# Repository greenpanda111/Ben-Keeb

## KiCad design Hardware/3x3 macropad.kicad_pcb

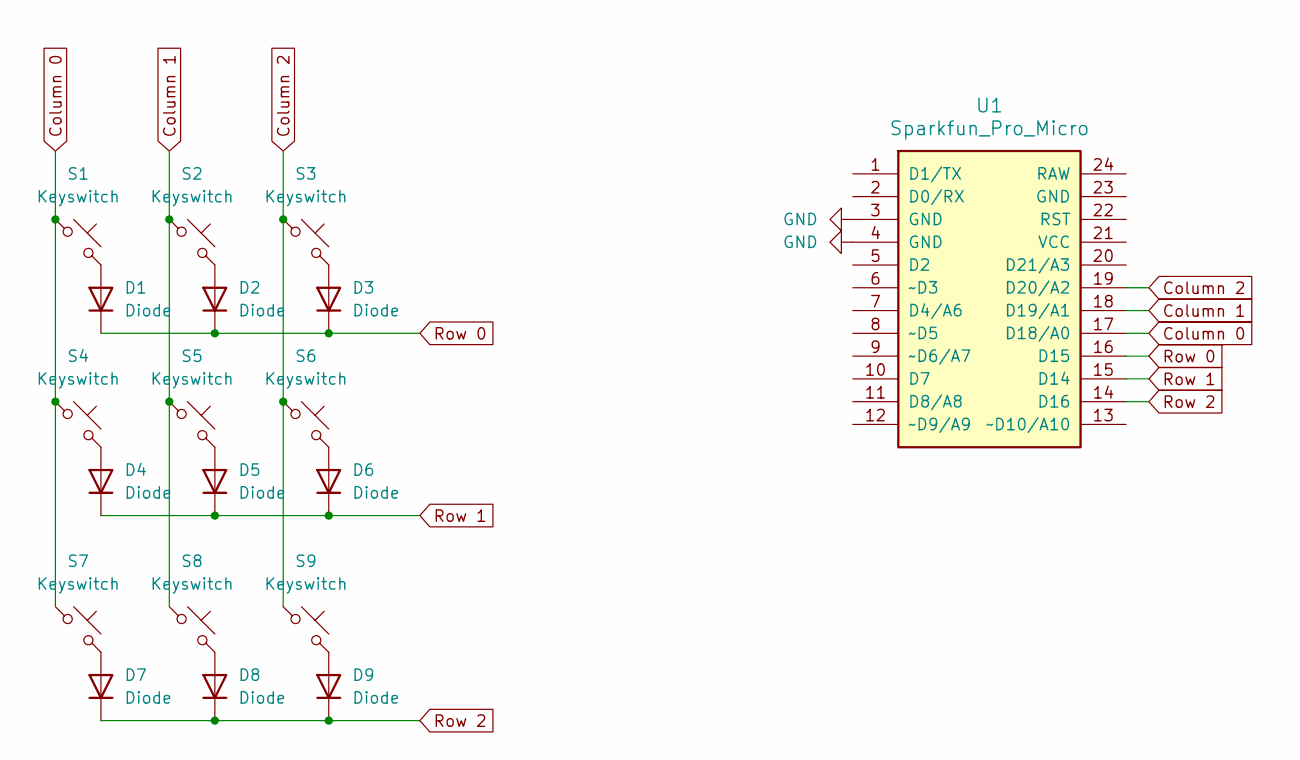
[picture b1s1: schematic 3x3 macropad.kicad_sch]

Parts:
D1, D2, D3, D4, D5, D6, D7, D8, D9: Diode; Diode_DO-35
S1, S2, S3, S4, S5, S6, S7, S8, S9: Keyswitch; MX_PCB_1.00u
U1: Sparkfun_Pro_Micro

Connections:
Column 0: S1.1, S4.1, S7.1, U1.17 (D18/A0)
Column 1: S2.1, S5.1, S8.1, U1.18 (D19/A1)
Column 2: S3.1, S6.1, S9.1, U1.19 (D20/A2)
GND: U1.3 (GND), U1.4 (GND)
unnamed: D1.2 (A), S1.2
unnamed: D2.2 (A), S2.2
unnamed: D3.2 (A), S3.2
unnamed: D4.2 (A), S4.2
unnamed: D5.2 (A), S5.2
unnamed: D6.2 (A), S6.2
unnamed: D7.2 (A), S7.2
unnamed: D8.2 (A), S8.2
unnamed: D9.2 (A), S9.2
Row 0: D1.1 (K), D2.1 (K), D3.1 (K), U1.16 (D15)
Row 1: D4.1 (K), D5.1 (K), D6.1 (K), U1.15 (D14)
Row 2: D7.1 (K), D8.1 (K), D9.1 (K), U1.14 (D16)

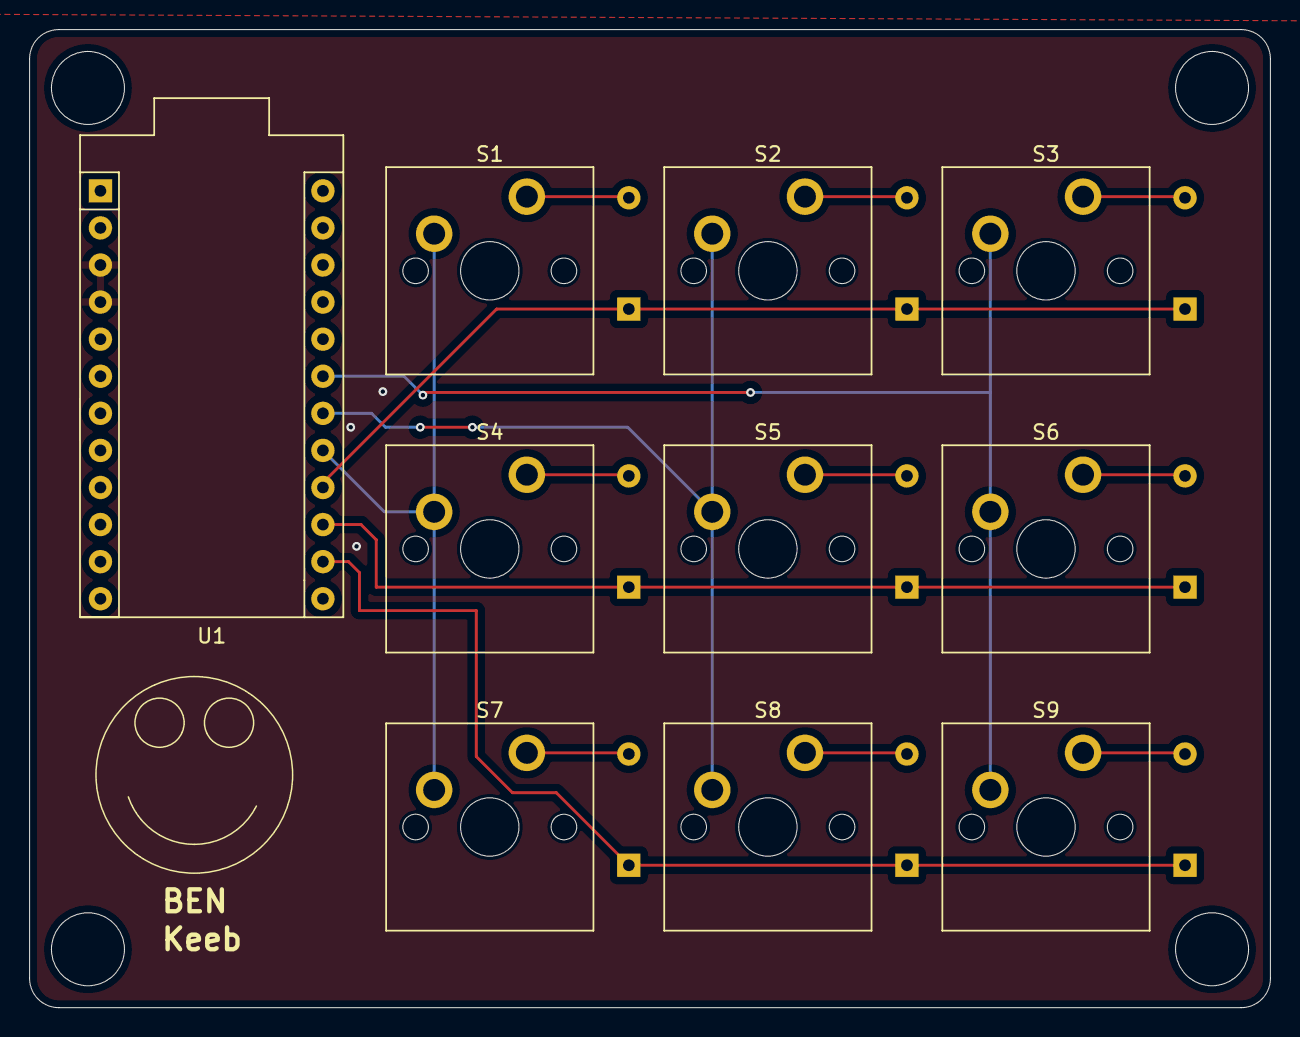
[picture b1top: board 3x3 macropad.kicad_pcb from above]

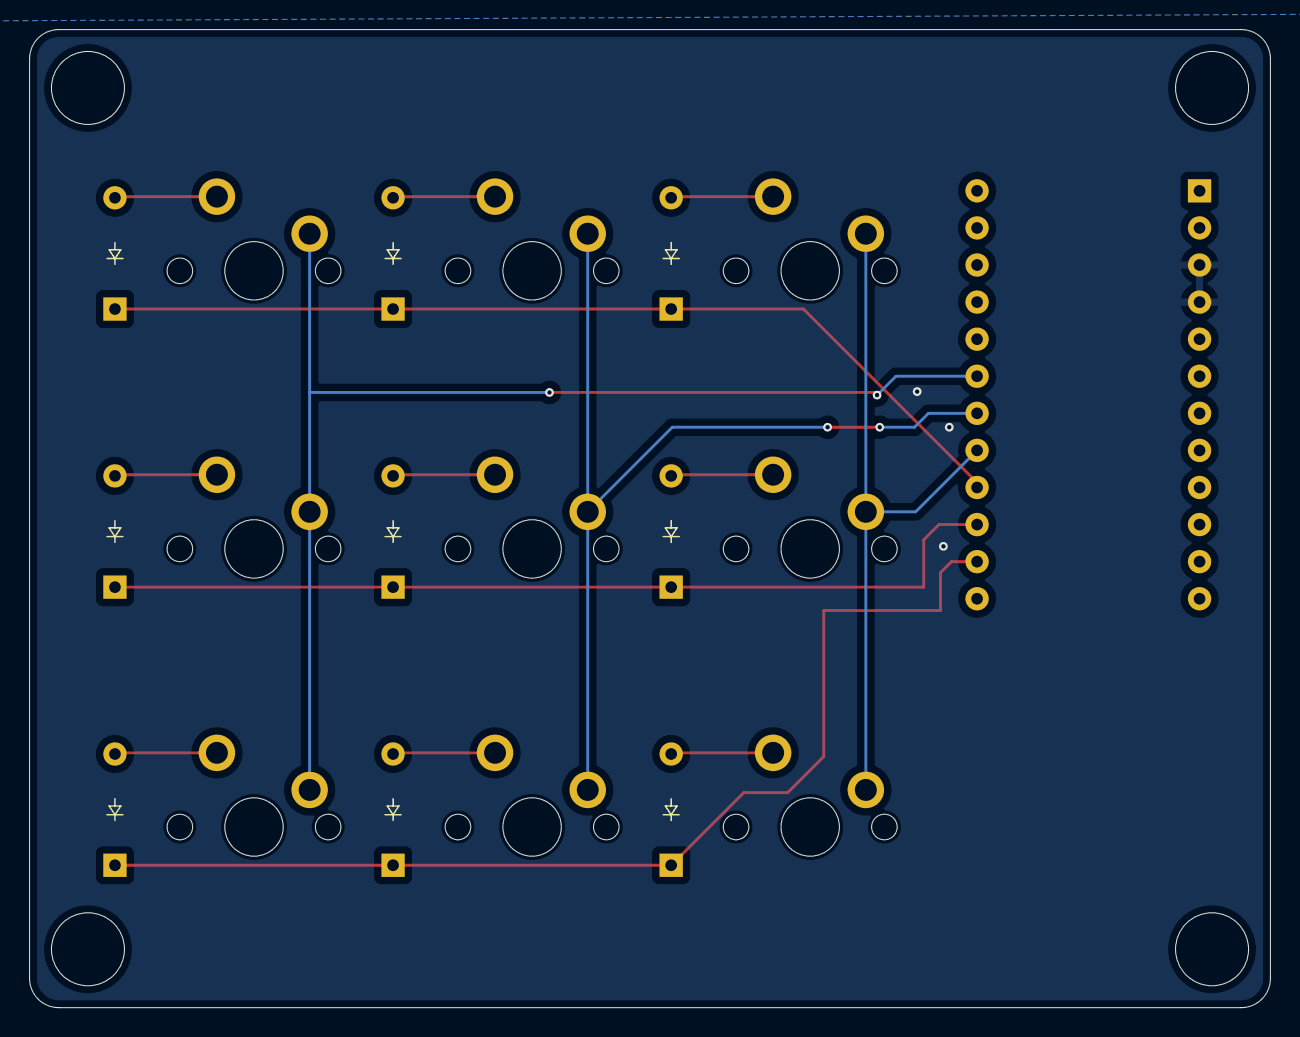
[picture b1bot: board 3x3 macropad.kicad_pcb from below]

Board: 2 copper layers, 85.0 x 67.0 mm, 19 parts (9 on the bottom side), 16 nets.

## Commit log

2024-11-19 PCB files
2024-11-19 Added hardware files to repo
